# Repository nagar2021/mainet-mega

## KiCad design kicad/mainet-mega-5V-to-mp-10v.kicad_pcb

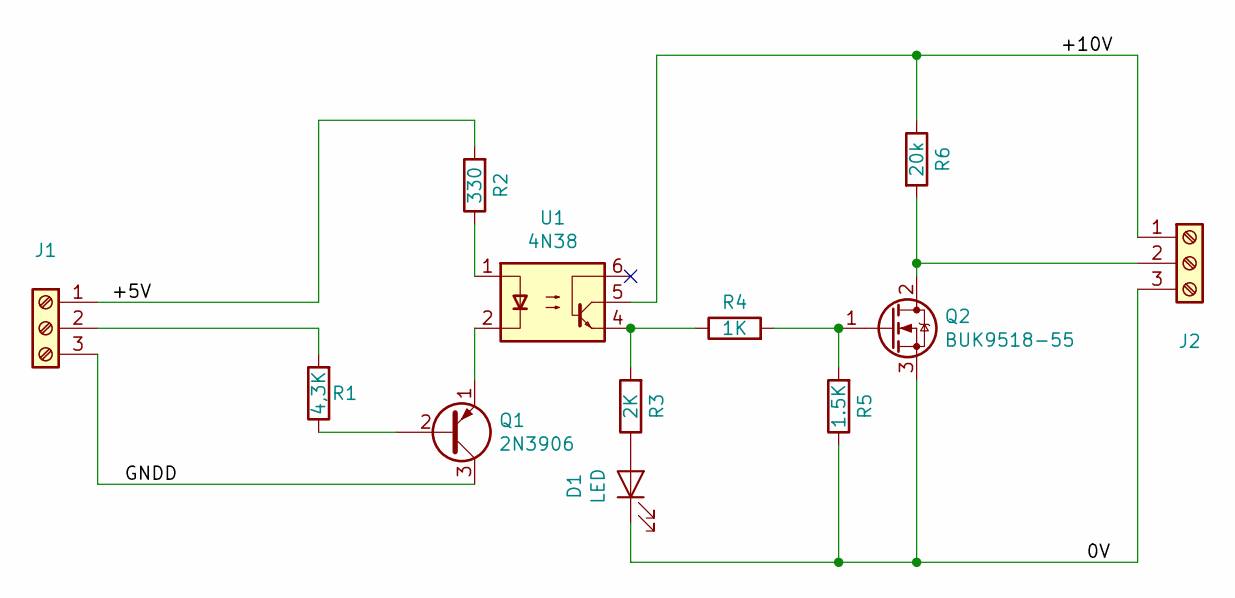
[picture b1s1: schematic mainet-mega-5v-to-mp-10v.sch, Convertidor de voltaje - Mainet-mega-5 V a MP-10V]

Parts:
D1: LED; LED_D5.0mm
J1, J2: Screw_Terminal_01x03; Altech_AK300_1x03_P5.00mm_45-Degree
Q1: 2N3906; TO-92_Inline
Q2: BUK9518-55; TO-220-3_Vertical
R1: 4,3K; R_Axial_DIN0207_L6.3mm_D2.5mm_P7.62mm_Horizontal
R2: 330; R_Axial_DIN0207_L6.3mm_D2.5mm_P7.62mm_Horizontal
R3: 2K; R_Axial_DIN0207_L6.3mm_D2.5mm_P7.62mm_Horizontal
R4: 1K; R_Axial_DIN0207_L6.3mm_D2.5mm_P7.62mm_Horizontal
R5: 1.5K; R_Axial_DIN0207_L6.3mm_D2.5mm_P7.62mm_Horizontal
R6: 20k; R_Axial_DIN0207_L6.3mm_D2.5mm_P7.62mm_Horizontal
U1: 4N38; DIP-6_W7.62mm

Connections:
/0V: D1.1 (K), J2.3, Q2.3 (S), R5.1
/+5V: J1.1, R2.2
/+10V: J2.1, R6.1, U1.5
/GNDD: J1.3, Q1.3 (C)
unnamed: D1.2 (A), R3.1
unnamed: J1.2, R1.2
unnamed: J2.2, Q2.2 (D), R6.2
unnamed: Q1.1 (E), U1.2
unnamed: Q1.2 (B), R1.1
unnamed: Q2.1 (G), R4.2, R5.2
unnamed: R2.1, U1.1
unnamed: R3.2, R4.1, U1.4

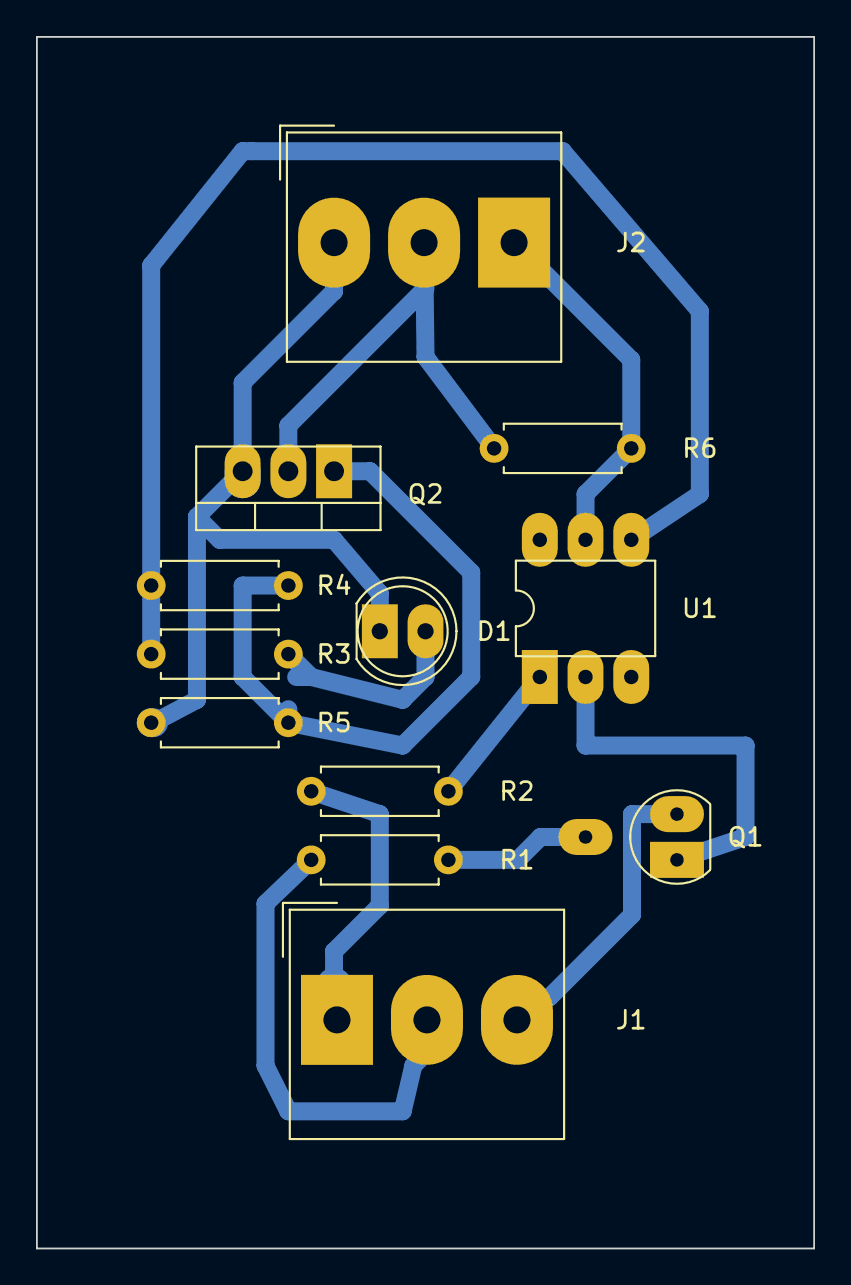
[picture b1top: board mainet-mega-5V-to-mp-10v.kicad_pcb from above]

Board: 2 copper layers, 43.2 x 67.3 mm, 12 parts (0 on the bottom side), 12 nets.

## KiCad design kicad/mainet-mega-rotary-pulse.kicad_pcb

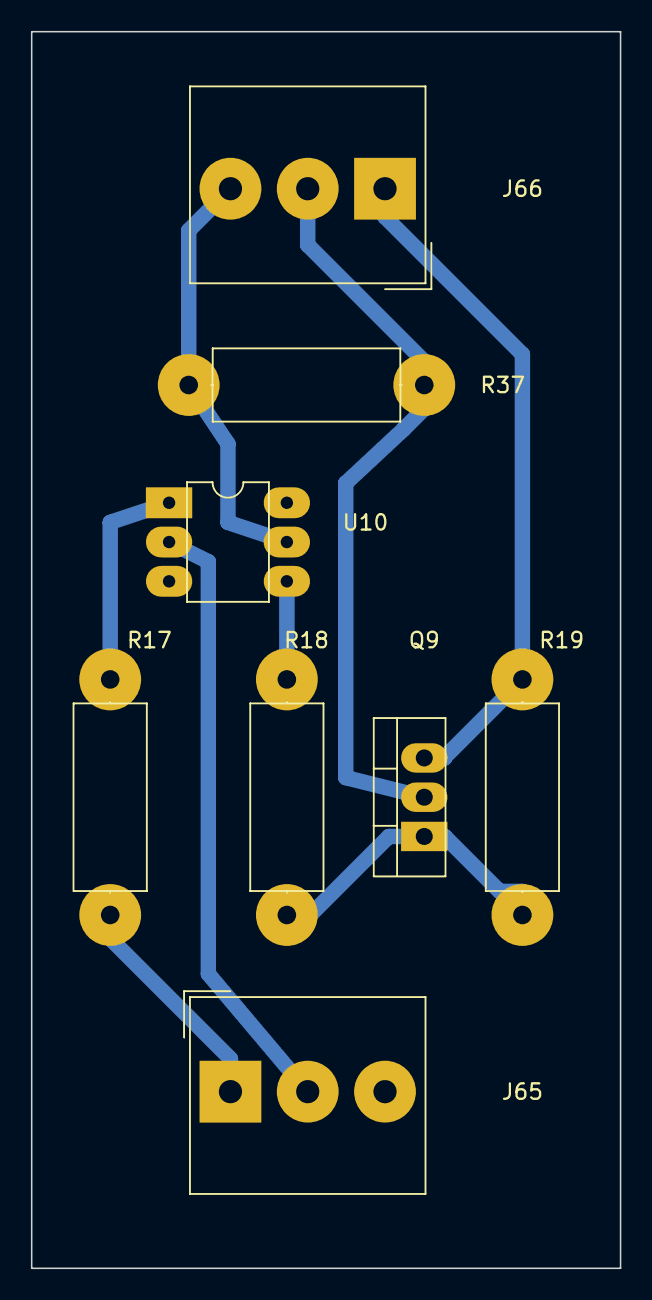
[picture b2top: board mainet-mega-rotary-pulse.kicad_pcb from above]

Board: 2 copper layers, 38.1 x 80.0 mm, 8 parts (0 on the bottom side), 8 nets.

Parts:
J65, J66: Screw_Terminal_01x03; Altech_AK300_1x03_P5.00mm_45-Degree
Q9: BUK9518-55; TO-220-3_Vertical
R17: 2.2K; R_Axial_DIN0414_L11.9mm_D4.5mm_P15.24mm_Horizontal
R18: 1K; R_Axial_DIN0414_L11.9mm_D4.5mm_P15.24mm_Horizontal
R19: 6.8K; R_Axial_DIN0414_L11.9mm_D4.5mm_P15.24mm_Horizontal
R37: 20k; R_Axial_DIN0414_L11.9mm_D4.5mm_P15.24mm_Horizontal
U10: 4N38; DIP-6_W7.62mm

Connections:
/+5V: J66.3, R37.1, U10.5
/+24V: J65.1, R17.2
/rotaryPulseOut-24V: J65.2, U10.2
/rotaryPulseOutput: J66.2, Q9.2, R37.2
GNDD: J66.1, Q9.3, R19.1
unnamed: Q9.1, R18.2, R19.2
unnamed: R17.1, U10.1
unnamed: R18.1, U10.4

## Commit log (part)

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2021-01-26 Eliminación de comentarios innecesarios
2021-01-26 Se agregaron archivos recomendados
2021-01-27 Kicad: Modificaciones menores esquemáticos
2021-01-27 Arduino: Modificación de pines de entrada y salida
    Se agregaron las entradas clutchChuck y brakeChuck
    y sus correspondientes salidas de 24VDC para controlar
    los mandriles neumáticos.
2021-01-27 Kicad: Eliminados _autosave
2021-01-29 Se agregó .gitignore al direcctorio kicad
2021-01-29 Actualización de .gitignore en el directorio raíz
2021-01-29 Correción en definición de pines de salida
2021-01-29 Actualización de kicad/.gitignore
2021-02-01 KiCAD: Se agregó el esquemático del circuito de traslación de voltaje del generador de pulsos de rotación
2021-02-01 KiCAD: Se agregó esquemáticos del módulo de coversión de voltaje de 5V a !0 V
2021-02-02 ARDUINO: Eliminación de comentarios innecesarios
2021-02-02 GLOBAL: Se agregaron archivos recomendados
2021-02-02 KICAD: Se agregó .gitignore al direcctorio kicad
2021-02-02 GLOBAL: Actualización de .gitignore en la raíz
2021-02-02 ARDUINO: Correción en def. de pines de salida
2021-02-02 KICAD: Actualización de kicad/.gitignore
2021-02-02 KiCAD: Se agregó título al esquemático del M400
2021-02-02 KICAD: Actualización de esquematicos del módulo de 8 relés de control
2021-02-02 Documentación pdf del módulo de relés
2021-03-08 Uso de un solo archivo .gitignore
2021-03-11 KICAD: Modificar frecuencyRefControl.sch
2021-03-11 KICAD: Modificar lowerClutchControl.sch
2021-03-11 KICAD: Modificar upperClutchControl.sch
2021-03-11 KICAD: Modificar mainet-mega-rotary-pulse.sch
2021-03-11 KICAD: Agregar PCB de mainet-mega-rotary-pulse
2021-03-11 KICAD: Agregar mainet-mega-rotary-pulse-cache.lib
2021-03-13 Modificar .gitignore Incluir archivos de .vscode/ y otros de KiCAD
2021-03-13 KICAD: Corregir mainet-mega-rotary-pulse.kicad_pcb
2021-03-16 Agregar .vscode/settings.json
2021-03-16 Actualizar .gitignore
2021-03-16 KICAD: Agregar esquemaático... mainet-mega-emergencyControlRelay.sch
2021-03-16 KICAD: Agregar cache de lib... mainet-mega-cache.lib
2021-03-16 .gitignore fix
2021-03-22 Agregar documentación sobre diseño de PCB
2021-03-23 KICAD: Agregar pdf del PCB mainet-mega-5v-to-mp-10v (negativo)
2021-03-24 KICAD: Corregir error en .gitignore No deben ignorarse los archivos *-rescue.lib
2021-03-24 KICAD: Corregir .gitignore Importante rastrear archivos *-rescue.lib
2021-03-24 KICAD: Corregir .gitignore
2021-03-24 KICAD: Eliminar kicad/.gitignore
2021-03-24 KICAD: Agregar archivos .lib
2021-03-24 KICAD: Agreagar sch de emergencyStopRelay
2021-03-25 Clean up ignored files
2021-03-25 KICAD: Fix .gitignore
2021-03-25 Clean up ignored files .lib
2021-03-25 KICAD: Actualizar sch Fecha y versión
2021-04-06 Corregir .gitignore para excluir archivos de sincronización de SyncToy
2021-04-07 KICAD: Actualizar fecha
2021-04-07 KICAD: Actualizar .sch
2021-04-07 KICAD: Actualizar esquemáticos
2021-04-07 Borrar pdf (PCB)
2021-04-07 KICAD: Incluir pdf de arcivos sch
2021-05-12 KICAD: Agregar bordes de corte mainet-mega-rotary-pulse.kicad_pcb
2021-05-12 KICAD: Agregar plano de tierra mainet-mega-rotary-pulse.kicad_pcb
2021-06-14 KICAD: Agregar esquemático del módulo YYNMOS-4
2021-06-15 KICAD: Agregar correcciones esquemáticos yynmos-4
2021-06-16 KICAD: Modificar mainet-mega-relay-driver-1.sch
2021-06-16 KICAD: Corregir kicad/mainet-mega-m400.sch
2021-06-16 KICAD: Modificar esquemático
2021-06-16 KICAD: Modificar esquemático m400
2021-06-17 KICAD: Eliminar mainet-mega-relay-3.sch
2021-06-17 KICAD: Agregar nuevo esquemático mainet-mega-regleta-conexiones-motores.sch
2021-06-17 KICAD: Actulizar .sch del M400
2021-06-17 KICAD: Agregar pdf info del módulo YYNMOS-4
2021-06-18 Agregar pdf con info del M400
2021-06-18 KICAD: Agregar cambios esquemáticos
2021-06-25 KICAD: Agregar cambios esquemático del generador rotacional de pulsos
2021-06-25 KICAD: Guardar cambio menor en sch
2021-06-25 KICAD: Guardar cambios sch del control de frecuencia M400
2021-06-25 KICAD: Agregar archivos pdf de sch nuevos
2021-06-28 DOC: Agregar documentación del RPGC (Rotery pulse Genertator)
2021-06-28 KICAD: Modificar sch del RPG
2021-06-29 KICAD: Incluir power jack en el .sch
2021-06-29 KICAD: Actualizar archivos sch
2021-07-01 KICAD: Agregar nuevo símbolo : +5V_Nextion
2021-07-01 KICAD: Actualizar el cache de las librerías
2021-07-01 KICAD: Actualizar .sch del display Nextion
2021-07-02 KICAD: Corregir pines de salida digital del Arduino para control de relés y pines de cableado con la pantalla Nextion
2021-07-02 ARDUINO: Corregir pines de salida digital para control de relés
2021-07-02 KICAD: Agregar correciones sch
2021-07-02 KICAD: Corregir pinout conector RPG
2021-07-02 KICAD: Actualizar archivo cache .lib
2021-07-06 KICAD: Agregar correcciones en .sch
2021-07-06 KICAD: AGregar cambios en .sch del controlador de frecuencia
2021-07-07 KICAD: Agregar cambios a .sch
2021-07-07 PDF: Agregar imagen terminales yynmos-4
2021-07-09 KICAD: Modificar sch del M400
2021-07-13 KICAD: Guardar cambios en sch RPG
2021-07-13 KICAD: Guardar cambios .sch frequencyRefControl
2021-07-13 KICAD: Agregar cvambios .sch controles tarjetas MP
2021-07-13 IMAGES: Cambiar yynmos-4.jpg de carpeta
2021-07-14 KICAD: Actualizar .sch regleta de conexiones
2021-07-14 KICAD: Actualizar .sch regleta conexión embragues
2021-07-14 KICAD: Actualizar .sch chuck embrague inferior
2021-07-14 KICAD: Actualizar .sch chunk del freno
2021-07-15 KICAD: Actualizar sch de la regleta de conexiones
2021-07-15 KICAD: Actualizar sch del pulsador de emergencia
2021-07-15 KICAD: Actualizar sch del diagrama a bloques
2021-07-15 KICAD: Actualizar el cache de librerías
2021-07-16 KICAD: Actualizar .sch de la regleta de conexiones de embragues y freno
2021-07-16 : Actualizar .sch diagrama de bloques
2021-07-16 KICAD: Reorganizar .sc regleta de conexiones
2021-07-16 KICAD: Reorganizar .sch relé de parada
2021-07-20 KICAD: Agregar conexiones de la Guía de banda regleta de conexiones
2021-07-20 KICAD: Actualizar .sch regleta de conexiones Agrega conexión para la guía de banda
2021-07-20 KICAD: Actualizar .sch manejadores de relés Agrega alimentación de +5V de dispositivos del lado del Arduino diferente a la salida de +5V del Arduino
2021-07-20 KICAD: Actualizar .sch general del proyecto
2021-07-21 PDF: Agrtegar hoja de datos ATmega
2021-07-21 KICAD: Corregir numeración pines Arduino de control de relés
2021-07-21 ARDUINO: Actualizar programa correcciones generales
2021-07-29 PDF: Incluir info de las valvulas solenoides 5 puertos 2 posiciones simple VFS2120-5D-02N
2021-07-29 ARDUINO: Actualizar programa
2021-07-30 KICAD: Correguir frequencyRefControl.sch conexión erronea en J72
2021-07-30 KICAD: Agregar User_enable_1 al .sch del M400. Así se puede inhibir su funcionamiento desde el SW machineEnable (User_machine_2) y desde el software Ambas señales deben ser HIGH para permitir el func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
2021-07-30 KICAD: Agregar .sch para usar el relé 8 para inhibir el M400 desde el software
2021-07-30 VSCODE: Actualizar settings del espaciop de trabajo
2021-08-04 ARDUINO: Modificar habilitación del conteo para usar interrupción en el conteo de pulsos
2021-08-05 ARDUINO: Modificar ISR del contador de pulsos
2021-08-06 KICAD: Actualizar pin de entrada del Arduino-mega que recibe la señal del generador rotacional de pulsos
2021-08-06 ARDUINO: Actualizar tipo de variable numeroDePulsos a long
2021-08-08 ARDUINO: Agregar función para reiniciar el contador de etiquetas
2021-08-09 IMAGES: Agregar imagenes del RPG
2021-08-09 KICAD: Agregar imagenes del RPG al .sch
2021-08-10 KICAD: Actualizar .sch del acondicionador de los pulsos del RPG de 24V a 5V
2021-08-12 ARDUINO: Agregar visualización del reinicio de conteo en la funcción trigger3()
2021-08-12 KICAD: Borrar mainet-rotary-pulse.pro
2021-08-12 KICAD: Cambiar .sch de frequencyRefControl se volvió al diseño original del PWM
2021-08-16 KICAD: Agregar valores resistencias
2021-08-17 ARDUINO: Actualizar .ino
2021-08-18 NEXTION: Establecer comunicación a 115200 y otros cambios en la programación. Se agrega entrada a la página 1 al tocar la caja del número de etiquetas por rollo, o la de número de etiquetas contadas.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
2021-08-18 ARDUINO: Establecer Serial2 a 115200 y otros: Agregar constantes para los colores usados en la pantalla Nextion y que son modificados desde el Arduino-mega. Se reordena las funciones triggerx()
2021-08-20 ARDUINO: Cambiar unsigned int por uint32_t
2021-08-20 NEXTION: Actualizar Program.s Se agregan condiciones iniciales faltantes
2021-08-20 ARDUINO: Agregar funciones trigger3...6
2021-08-20 NEXTION: Agregar funciones trigger 4...6
2021-08-23 NEXTION: Corregir comentarios
2021-08-24 ARDUINO: Cambiar valores iniciales en Nextion
2021-08-24 NEXTION: Corregir comentarios en Program.s
2021-08-24 DEBUG:
2021-08-25 ARDUINO: Agregar función de diagnóstico
2021-08-26 ARDUINO: Cambiar uint32_t por unsigned long
2021-08-26 NEXTION: Agregar trigguer3()
2021-08-26 NEXTION: Cambiar a global las variables asociadas a los indicadores de freno, velocidad, y embragues
2021-08-26 ARDUINO: Definir como uint32_t todas las variables asociadas a propiedades numéricas de componentes Nextion
2021-08-27 ARDUINO: Agregar función de frenado auto
2021-08-30 NEXTION: Agregar imagenes rebobinado
2021-08-31 NEXTION: Agregar nueva fuente
2021-08-31 NEXTION: Agregar modificaciones diseño pantalla
2021-08-31 NEXTION: Cambiar a global variables
2021-08-31 ARDUINO: Agregar función de parada
2021-09-01 ARDUINO: Agregar funciones nuevas
2021-09-01 NEXTION: Agregar funciones nuevas
2021-09-02 FRENADO: Cambios en funciones
2021-09-06 NEXTION: Corregir error en C.SW0
2021-09-06 ARDUINO: Correcciones en frenado
2021-09-07 ARDUINO: Cambiar etiquetaDeFrenadoNum a uint32_t
2021-09-07 ARDUINO: Cambiar no. función trigguer
2021-09-08 ARDUINO/NEXTION: Cambiar lógica frenado
2021-09-08 ARDUINO: Agregar reinicio del conteo de etiquetas al desconectar el mandril del embrague
2021-09-09 ARDUINO: Cambiar dutyCycleMin a 15%
2021-09-09 NEXTION: Agregar caja para visualización... de la velocidad del material en m/min
2021-09-10 NEXTION: Modificar cálculo etiqueta de frenado al 90% del número de etiquetas por rollo
2021-09-16 ARDUINO: Agregar cálculo velocidad m/min
2021-09-16 ARDUINO: Corregir error factor de conversión de unidades
2021-09-21 ARDUINO: Agregar variables lógicas para depuración
2021-09-22 ARDUINO: Modificar calcularVelocidad
2021-09-23 ARDUINO: Unificar puerto a COM4 en todos los PC uisados
2021-09-23 ARDUINO: Eliminar espacios en blanco al final de línea
2021-09-24 KICAD: Actualizar librerias cache y rescue
2021-09-24 ARDUINO: Agregar función de cambio de giro
2021-09-29 ARDUINO: Agregar función checkStartRun Se agrega un SW para marcha hacia adelante y reversa
2021-09-29 ARDUINO: Modificar preferencias arduino
2021-09-29 ARDUINO: Agregar las fns: checkRunReverse() y checkRunOff() y modificar checkRunForward() para implementar el cambio de giro
2021-09-30 ARDUINO: Borrar algunos comentarios innecesarios
2021-09-30 ARDUINO: Modificar ciclo de trabajo mínimo al 15%
2021-10-01 ARDUINO: Modificar funciones de verificación de estado de los mandriles de los embragues y del freno
2021-10-01 NEXTION: Modificar campos FRENO y EMBRAGUES a global para modificar color desde el Arduino
2021-10-04 NEXTION: Agregar imagenes nuevas indicadores
2021-10-05 NEXTION: Agregar opciones para el cálculo por defecto de la etiqueta de frenado: -5, -10, -15, -20 % del número de etiquetas por rollo
2021-10-05 NEXTION/ARDUINO: Agregar opciones para fijar el ciclo útil mínimo (10, 15,20y 25%)
2021-10-06 NEXTION: Corregir error en calculo 80% etiqueta de frenado
2023-05-10 Agregar capa anterior de serigrafía
2023-05-10 Corregir numeración de pines J65
2023-05-10 Agregar archivo de serigrafia anterior
2023-05-10 Actualizar archivo .pro Cambio de pines en J65
2023-05-11 Agregar archivo capa trasera de Cu
2023-05-11 Modificar pcb
2023-05-11 Borrar pdf/pdf-silks/mainet-mega-rotary-pulse-silk
2023-05-11 Actualizar librería cache
2023-06-02 Corregir numeración de pines terminales J2 / PCB
2023-06-02 Corregir numeración de pines en J2 tarjetas PWM
